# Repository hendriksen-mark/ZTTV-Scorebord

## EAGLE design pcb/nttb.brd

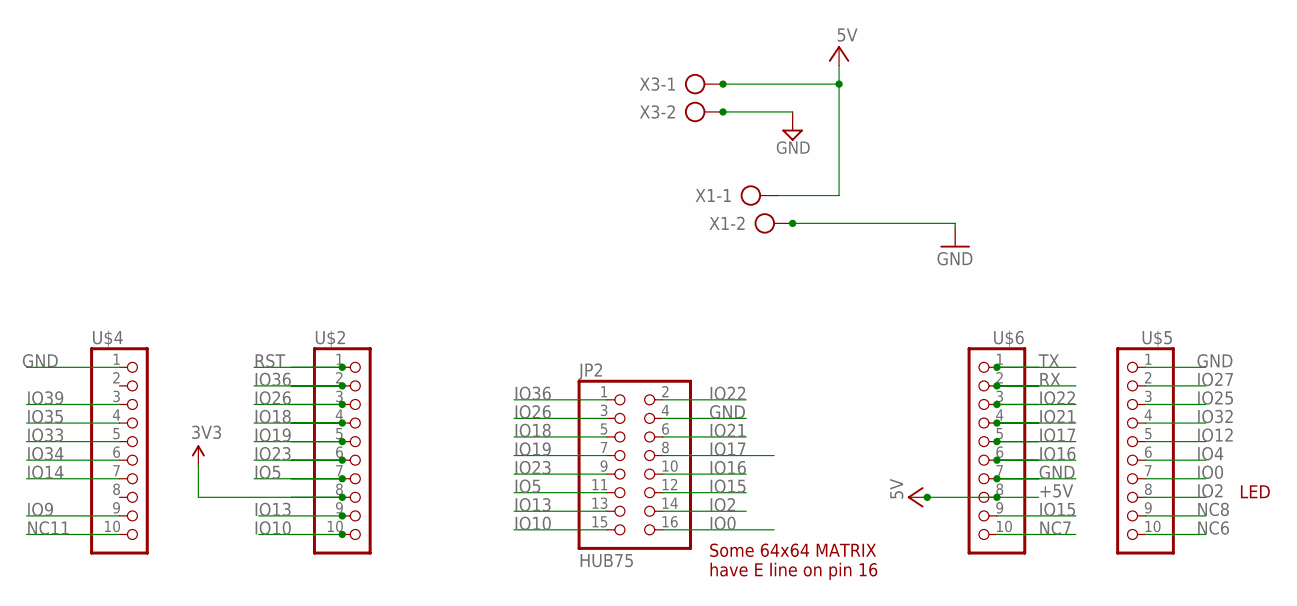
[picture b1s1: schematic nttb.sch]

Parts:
JP2: HUB75; 2X08
U$2, U$4, U$5, U$6: PINHD-1X10; 1X10-BIG
X1, X3: AK500/2

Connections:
3V3: U$2.8
+5V: U$6.8, X1.1, X3.1
GND: JP2.4, U$4.1, U$5.1, U$6.7, X1.2, X3.2
IO0: JP2.16, U$5.7
IO2: JP2.14, U$5.8
IO4: U$5.6
IO5: JP2.11, U$2.7
IO9: U$4.9
IO10: JP2.15, U$2.10
IO12: U$5.5
IO13: JP2.13, U$2.9
IO14: U$4.7
IO15: JP2.12, U$6.9
IO16: JP2.10, U$6.6
IO17: JP2.8, U$6.5
IO18: JP2.5, U$2.4
IO19: JP2.7, U$2.5
IO21: JP2.6, U$6.4
IO22: JP2.2, U$6.3
IO23: JP2.9, U$2.6
IO25: U$5.3
IO26: JP2.3, U$2.3
IO27: U$5.2
IO32: U$5.4
IO33: U$4.5
IO34: U$4.6
IO35: U$4.4
IO36: JP2.1, U$2.2
IO39: U$4.3
NC6: U$5.10
NC7: U$6.10
NC8: U$5.9
NC11: U$4.10
RST: U$2.1
RX: U$6.2
TX: U$6.1

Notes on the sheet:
Some 64x64 MATRIX have E line on pin 16
LED

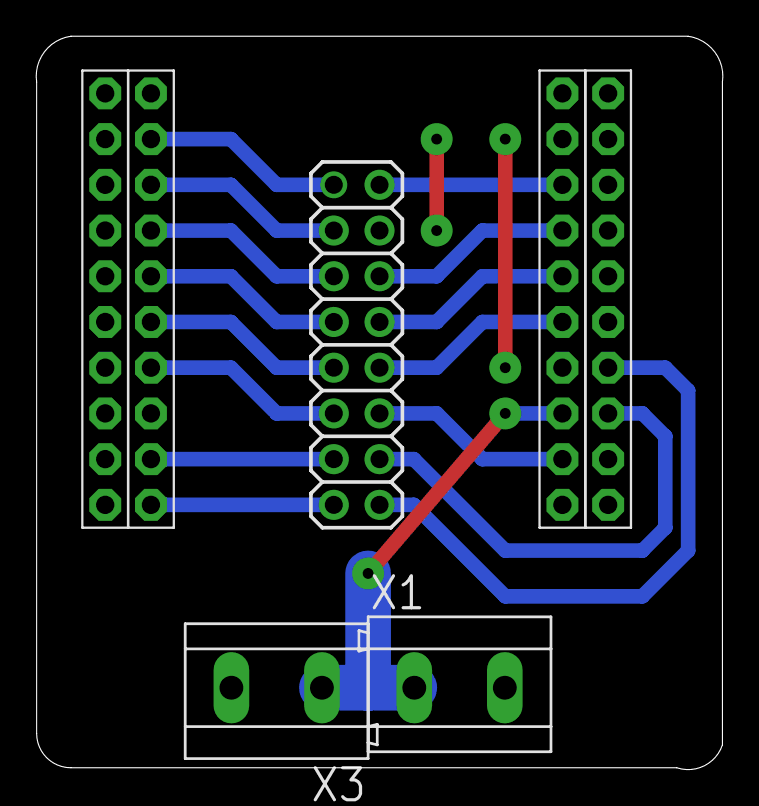
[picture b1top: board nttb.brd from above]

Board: 2 copper layers, 38.1 x 40.7 mm, 7 parts (0 on the bottom side), 17 nets.

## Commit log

2024-10-17 Update code for ESP32
2024-10-28 test of 64X32 panel
2024-10-28 add PCB
2024-11-02 Working proof of concept
2024-11-02 Cleanup
2024-11-03 Kleine bugfix
2024-11-03 Small bugfix & cleanup
2024-11-04 qrcode
2024-11-04 make variable for ssid and pass
2024-11-06 Rename to ZTTV
2024-11-10 WIFI does not provide a gateway
2024-11-17 update
    add debuglog.
    change wifi behavior.
    add /sbbanner.
2024-12-30 add gui
2024-12-30 update gui
2025-04-19 update generator
2025-04-19 update for `beker` in gui
2025-04-19 rename
2025-04-19 add translation

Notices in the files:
parts and their libraries:
microbuilder: This work is placed in the public domain, and may be freely used for commercial and non-commercial work with the following conditions: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
